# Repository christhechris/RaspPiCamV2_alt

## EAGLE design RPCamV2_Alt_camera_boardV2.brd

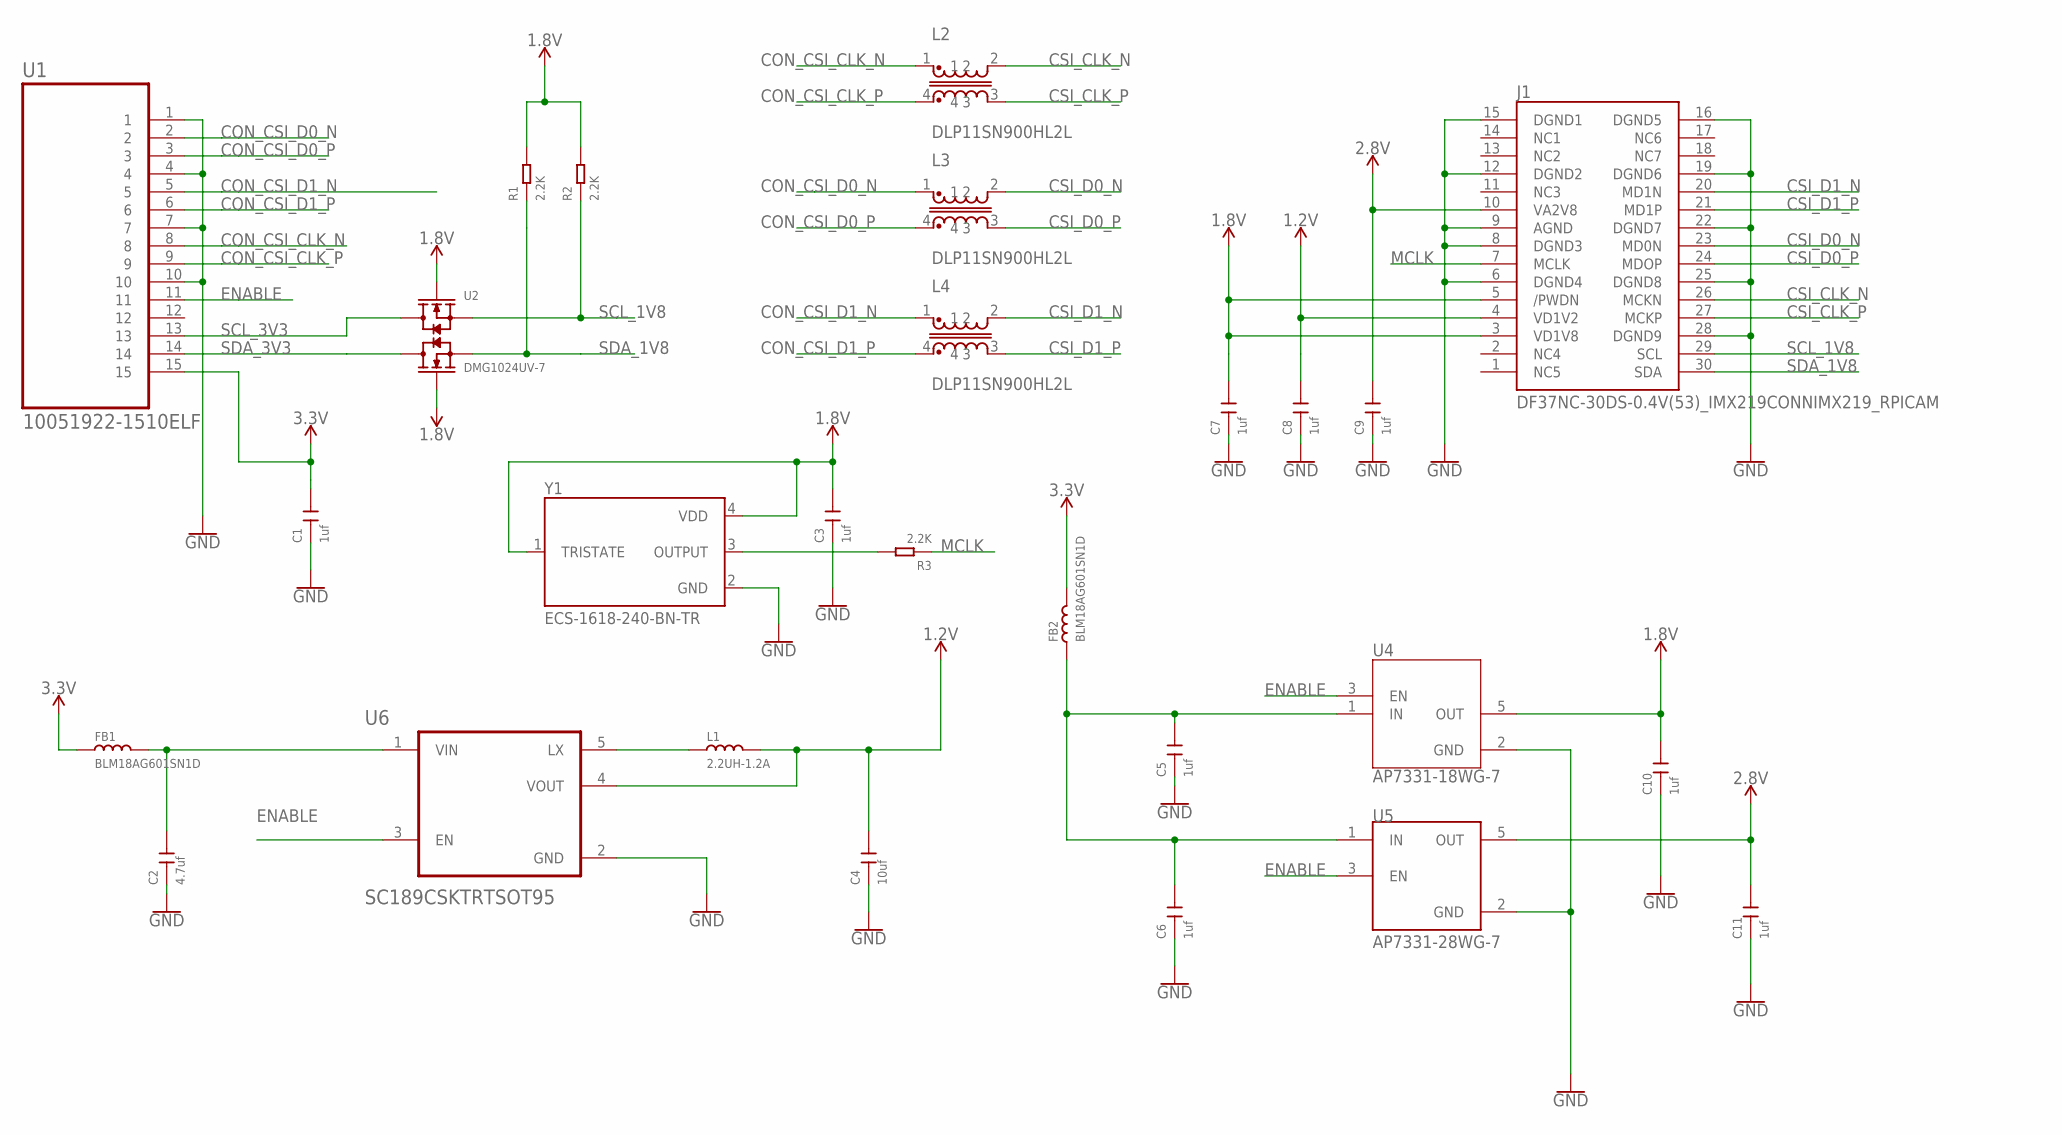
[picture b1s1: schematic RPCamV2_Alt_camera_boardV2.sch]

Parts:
C1, C3, C5, C6, C7, C8, C9, C10, C11: 1uf; C0402K
C2: 4.7uf; C0603
C4: 10uf; C2012
FB1, FB2: BLM18AG601SN1D; BEADC1608X80
J1: DF37NC-30DS-0.4V(53)_IMX219CONNIMX219_RPICAM; HRS_DF37NC-30DS-0.4V(53)_IMX219
L1: 2.2UH-1.2A; L0805
L2, L3, L4: DLP11SN900HL2L; INDC1210X09
R1, R2, R3: 2.2K; R0402
U1: 10051922-1510ELF; FCI_10051922-1510ELF
U2: DMG1024UV-7; SOT50P162X60-6N
U4: AP7331-18WG-7; SOT95P285X145-5N
U5: AP7331-28WG-7; SOT95P285X145-5N
U6: SC189CSKTRTSOT95; SOT95P285X145-5N
Y1: ECS-1618-240-BN-TR; XTAL_ECS-1618-060-BN-TR

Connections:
1.2V: C4.2, C8.2, J1.4 (VD1V2), L1.2, U6.4 (VOUT)
1.8V: C3.2, C7.2, C10.2, J1.3 (VD1V8), J1.5 (/PWDN), R1.2, R2.2, U2.G1 (G0), U2.G2 (G1), U4.5 (OUT), Y1.1 (TRISTATE), Y1.4 (VDD)
2.8V: C9.2, C11.2, J1.10 (VA2V8), U5.5 (OUT)
3V3: C1.2, FB1.1, FB2.2, U1.15
CON_CSI_CLK_N: L2.1, U1.8
CON_CSI_CLK_P: L2.4, U1.9
CON_CSI_D0_N: L3.1, U1.2
CON_CSI_D0_P: L3.4, U1.3
CON_CSI_D1_N: L4.1, U1.5
CON_CSI_D1_P: L4.4, U1.6
CSI_CLK_N: J1.26 (MCKN), L2.2
CSI_CLK_P: J1.27 (MCKP), L2.3
CSI_D0_N: J1.23 (MD0N), L3.2
CSI_D0_P: J1.24 (MDOP), L3.3
CSI_D1_N: J1.20 (MD1N), L4.2
CSI_D1_P: J1.21 (MD1P), L4.3
ENABLE: U1.11, U4.3 (EN), U5.3 (EN), U6.3 (EN)
GND: C1.1, C2.1, C3.1, C4.1, C5.1, C6.1, C7.1, C8.1, C9.1, C10.1, C11.1, J1.6 (DGND4), J1.8 (DGND3), J1.9 (AGND), J1.12 (DGND2), J1.15 (DGND1), J1.16 (DGND5), J1.19 (DGND6), J1.22 (DGND7), J1.25 (DGND8), J1.28 (DGND9), U1.1, U1.4, U1.7, U1.10, U4.2 (GND), U5.2 (GND), U6.2 (GND), Y1.2 (GND)
IN_PR: C5.2, C6.2, FB2.1, U4.1 (IN), U5.1 (IN)
MCLK: J1.7 (MCLK), R3.1
unnamed: C2.2, FB1.2, U6.1 (VIN)
unnamed: R3.2, Y1.3 (OUTPUT)
unnamed: L1.1, U6.5 (LX)
SCL_1V8: J1.29 (SCL), R2.1, U2.S2 (S1)
SCL_3V3: U1.13, U2.D2 (D1)
SDA_1V8: J1.30 (SDA), R1.1, U2.S1 (S0)
SDA_3V3: U1.14, U2.D1 (D0)

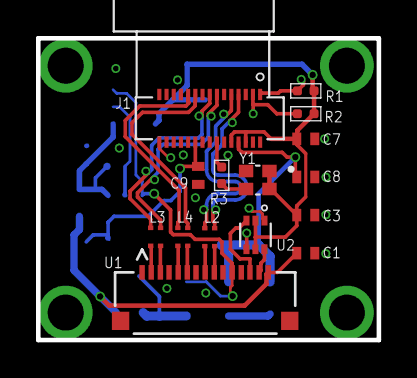
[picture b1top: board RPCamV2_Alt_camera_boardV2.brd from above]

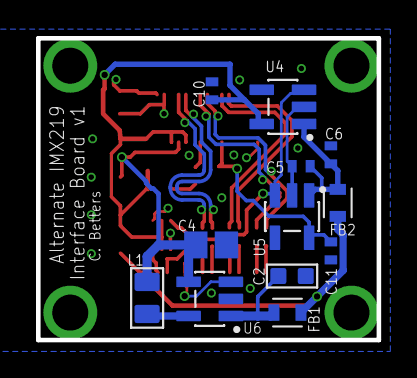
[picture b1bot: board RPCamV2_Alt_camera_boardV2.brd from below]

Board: 4 copper layers, 18.9 x 16.8 mm, 27 parts (12 on the bottom side), 27 nets.

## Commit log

2019-02-27 init commit
2019-03-05 part lists
2019-03-21 macrogab ordered
2019-03-21 swap 1.2V power regulator
2019-03-21 update part numbers
2019-04-15 ordered version.
